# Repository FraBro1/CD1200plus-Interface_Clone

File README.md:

# CD1200plus-Interface_Clone
Clone of the AlfaData CD1200+ PCMCIA IDE Interface for Amiga Computers

It was created using Eagle 8.3.1 (free edition) or previous versions
on 16.04.2019

Re-engineering the traces of the original pcb by close inspection and sometimes continuity checks.
There is no warranty for wether or not the connections i found are accurate or complete.

please keep in mind this is a hobby project.

There is no BOM provided at the moment.

[![CC BY-SA 4.0][cc-by-sa-shield]][cc-by-sa]

This work is licensed under a
[Creative Commons Attribution-ShareAlike 4.0 International License][cc-by-sa].

[![CC BY-SA 4.0][cc-by-sa-image]][cc-by-sa]

[cc-by-sa]: http://creativecommons.org/licenses/by-sa/4.0/
[cc-by-sa-image]: https://licensebuttons.net/l/by-sa/4.0/88x31.png
[cc-by-sa-shield]: https://img.shields.io/badge/License-CC%20BY--SA%204.0-lightgrey.svg

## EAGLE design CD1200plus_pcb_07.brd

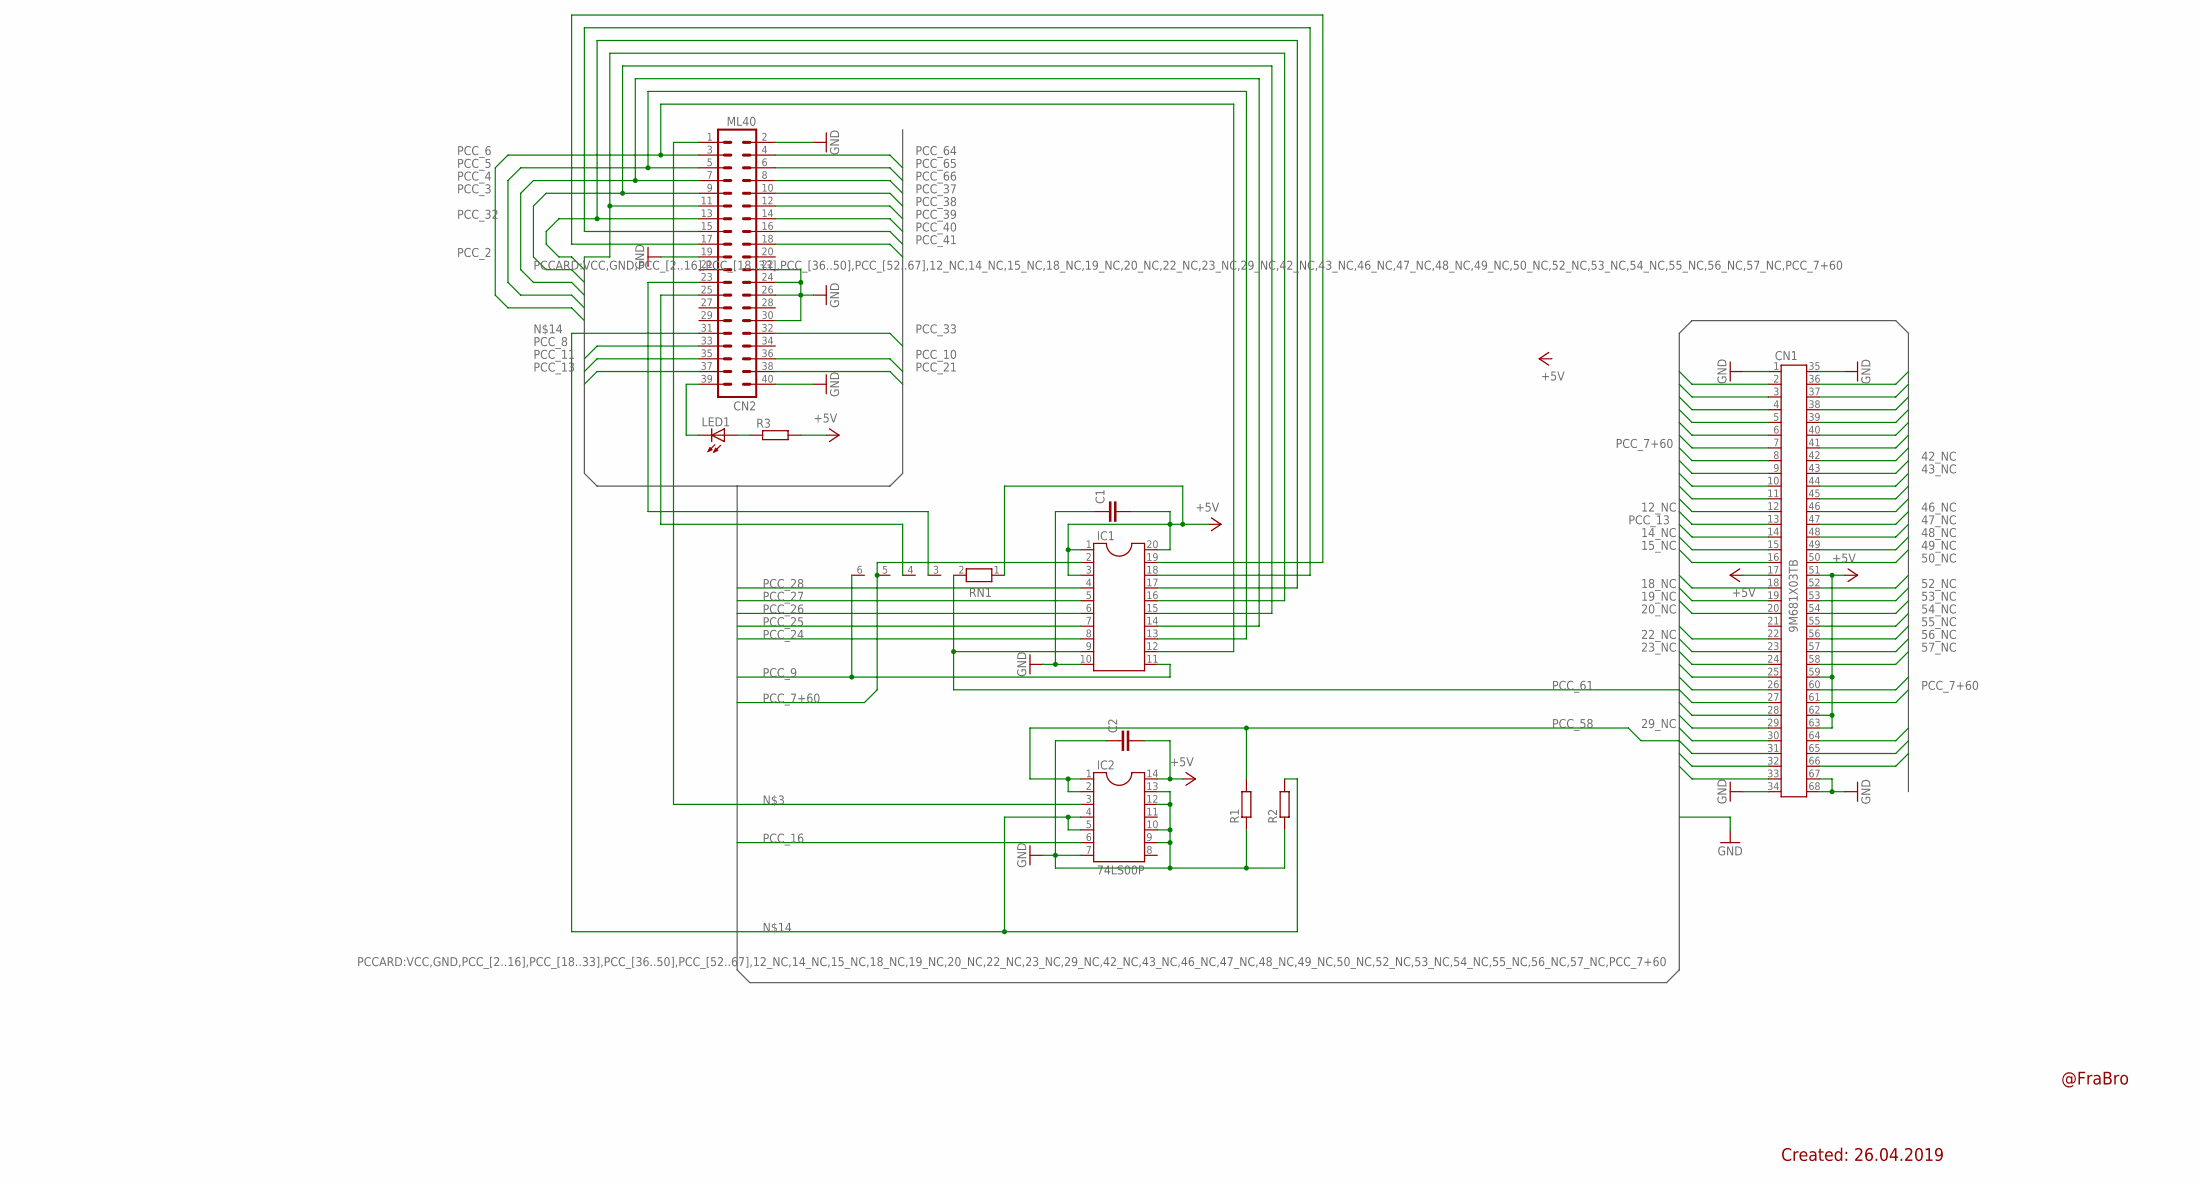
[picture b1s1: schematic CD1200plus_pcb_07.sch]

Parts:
C1, C2: C-EU050-035X075; C050-035X075
CN1: 9M681X03TB; 9M681X03
CN2: ML40
IC1: DIL20
IC2: 74LS00P; DIL14
LED1: LEDSML1206; SML1206
R1, R2, R3: R-EU_M1206; M1206
RN1: RN05; RN-6

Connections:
12_NC: CN1.12
14_NC: CN1.14
15_NC: CN1.15
18_NC: CN1.18
19_NC: CN1.19
20_NC: CN1.20
22_NC: CN1.22
23_NC: CN1.23
29_NC: CN1.29
42_NC: CN1.42
43_NC: CN1.43
46_NC: CN1.46
47_NC: CN1.47
48_NC: CN1.48
49_NC: CN1.49
50_NC: CN1.50
52_NC: CN1.52
53_NC: CN1.53
54_NC: CN1.54
55_NC: CN1.55
56_NC: CN1.56
57_NC: CN1.57
+5V: C1.2, C2.2, CN1.17, CN1.51, CN1.59, CN1.62, CN1.63, IC1.1, IC1.3, IC1.20, IC2.14, R3.2, RN1.1
GND: C1.1, C2.1, CN1.1, CN1.34, CN1.35, CN1.67, CN1.68, CN2.2, CN2.19, CN2.22, CN2.24, CN2.26, CN2.30, CN2.40, IC1.10, IC2.7, IC2.9, IC2.10, IC2.12, IC2.13, R1.1, R2.1
unnamed: CN2.23, RN1.3
unnamed: CN2.25, RN1.4
unnamed: CN2.1, IC2.3
unnamed: LED1.A, R3.1
unnamed: CN2.39, LED1.C
unnamed: CN2.15, IC1.18
unnamed: CN2.17, IC1.19
unnamed: CN2.31, IC2.4, IC2.5, R2.2
PCC_2: CN1.2, CN2.11, IC1.16
PCC_3: CN1.3, CN2.9, IC1.15
PCC_4: CN1.4, CN2.7, IC1.14
PCC_5: CN1.5, CN2.5, IC1.13
PCC_6: CN1.6, CN2.3, IC1.12
PCC_7+60: CN1.7, CN1.60, IC1.2, RN1.5
PCC_8: CN1.8, CN2.33
PCC_9: CN1.9, IC1.11, RN1.6
PCC_10: CN1.10, CN2.36
PCC_11: CN1.11, CN2.35
PCC_13: CN1.13, CN2.37
PCC_16: CN1.16, IC2.6
PCC_21: CN2.38
PCC_24: CN1.24, IC1.8
PCC_25: CN1.25, IC1.7
PCC_26: CN1.26, IC1.6
PCC_27: CN1.27, IC1.5
PCC_28: CN1.28, IC1.4
PCC_30: CN1.30
PCC_31: CN1.31
PCC_32: CN1.32, CN2.13, IC1.17
PCC_33: CN1.33, CN2.32
PCC_36: CN1.36
PCC_37: CN1.37, CN2.10
PCC_38: CN1.38, CN2.12
PCC_39: CN1.39, CN2.14
PCC_40: CN1.40, CN2.16
PCC_41: CN1.41, CN2.18
PCC_44: CN1.44
PCC_45: CN1.45
PCC_58: CN1.58, IC2.1, IC2.2, R1.2
PCC_61: CN1.61, IC1.9, RN1.2
PCC_64: CN1.64, CN2.4
PCC_65: CN1.65, CN2.6
PCC_66: CN1.66, CN2.8

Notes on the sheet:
@FraBro
Created: 26.04.2019

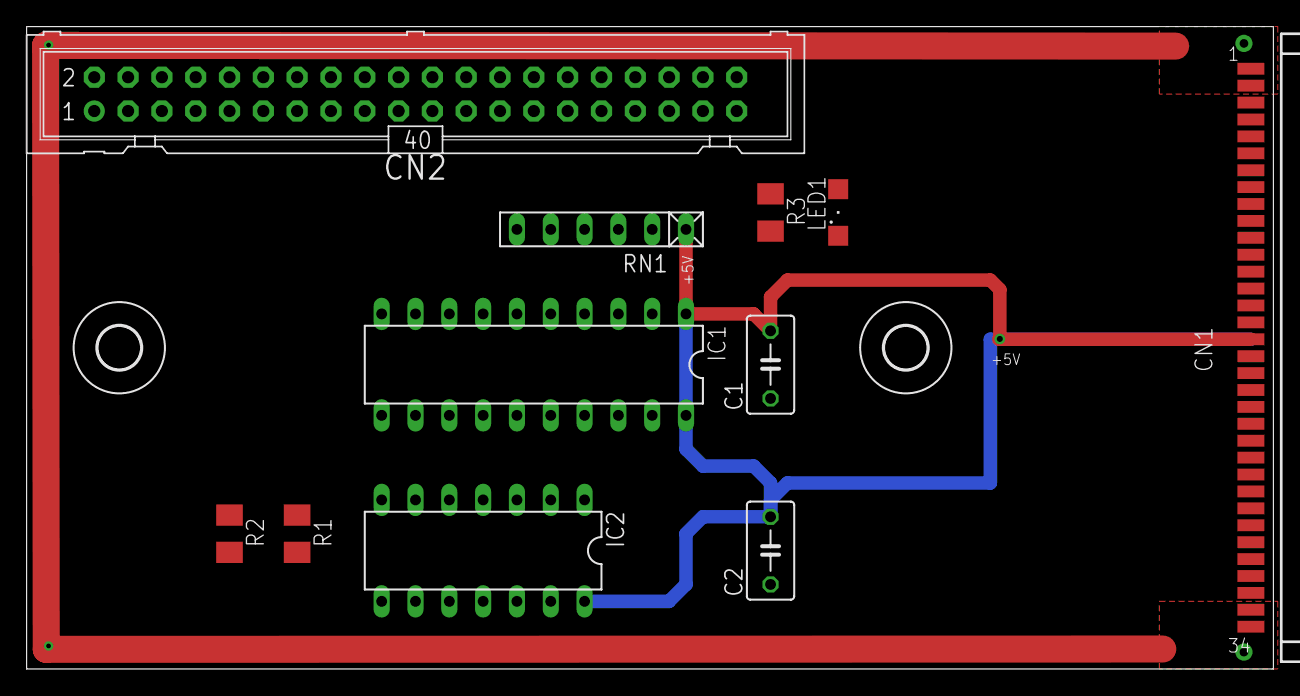
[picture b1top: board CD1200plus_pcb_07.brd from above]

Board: 2 copper layers, 93.7 x 48.2 mm, 13 parts (0 on the bottom side), 39 nets.

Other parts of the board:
U$1, U$2: 3,2

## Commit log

2023-09-15 added pictures
2023-09-15 cropped pic
2023-09-15 cropped
2023-09-17 Updated files
2023-09-17 added license
2023-09-20 created schematic PDF
2023-09-30 Delete CD1200plus_pcb_07.brd
    deleted because of incomplete routing; doesn't serve any purpose at the moment.
